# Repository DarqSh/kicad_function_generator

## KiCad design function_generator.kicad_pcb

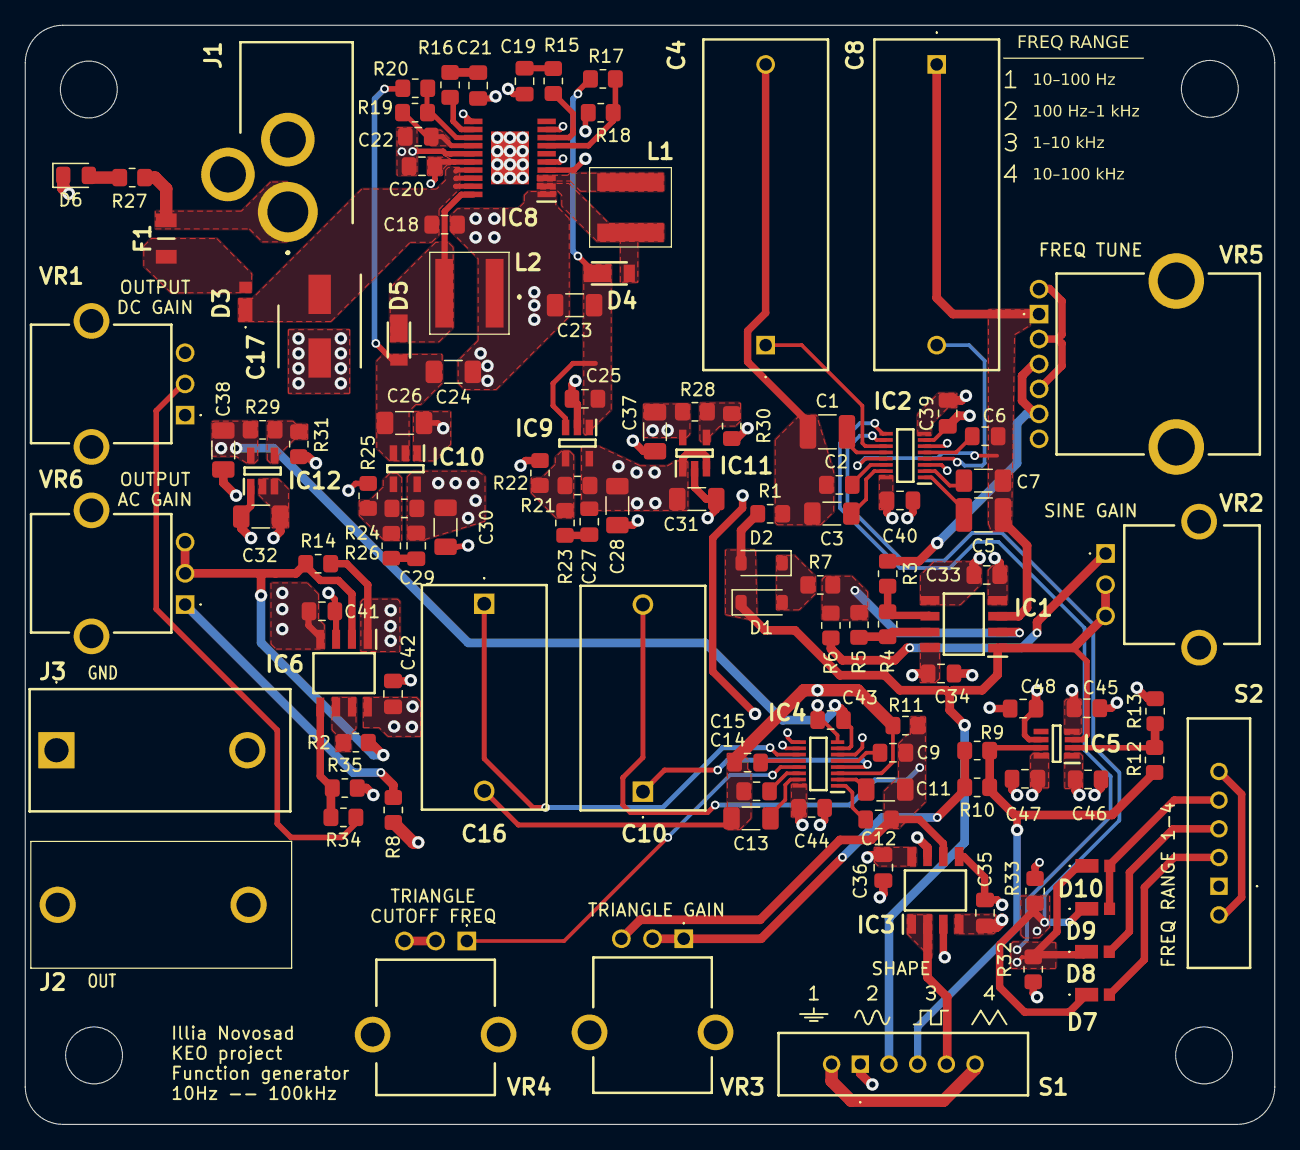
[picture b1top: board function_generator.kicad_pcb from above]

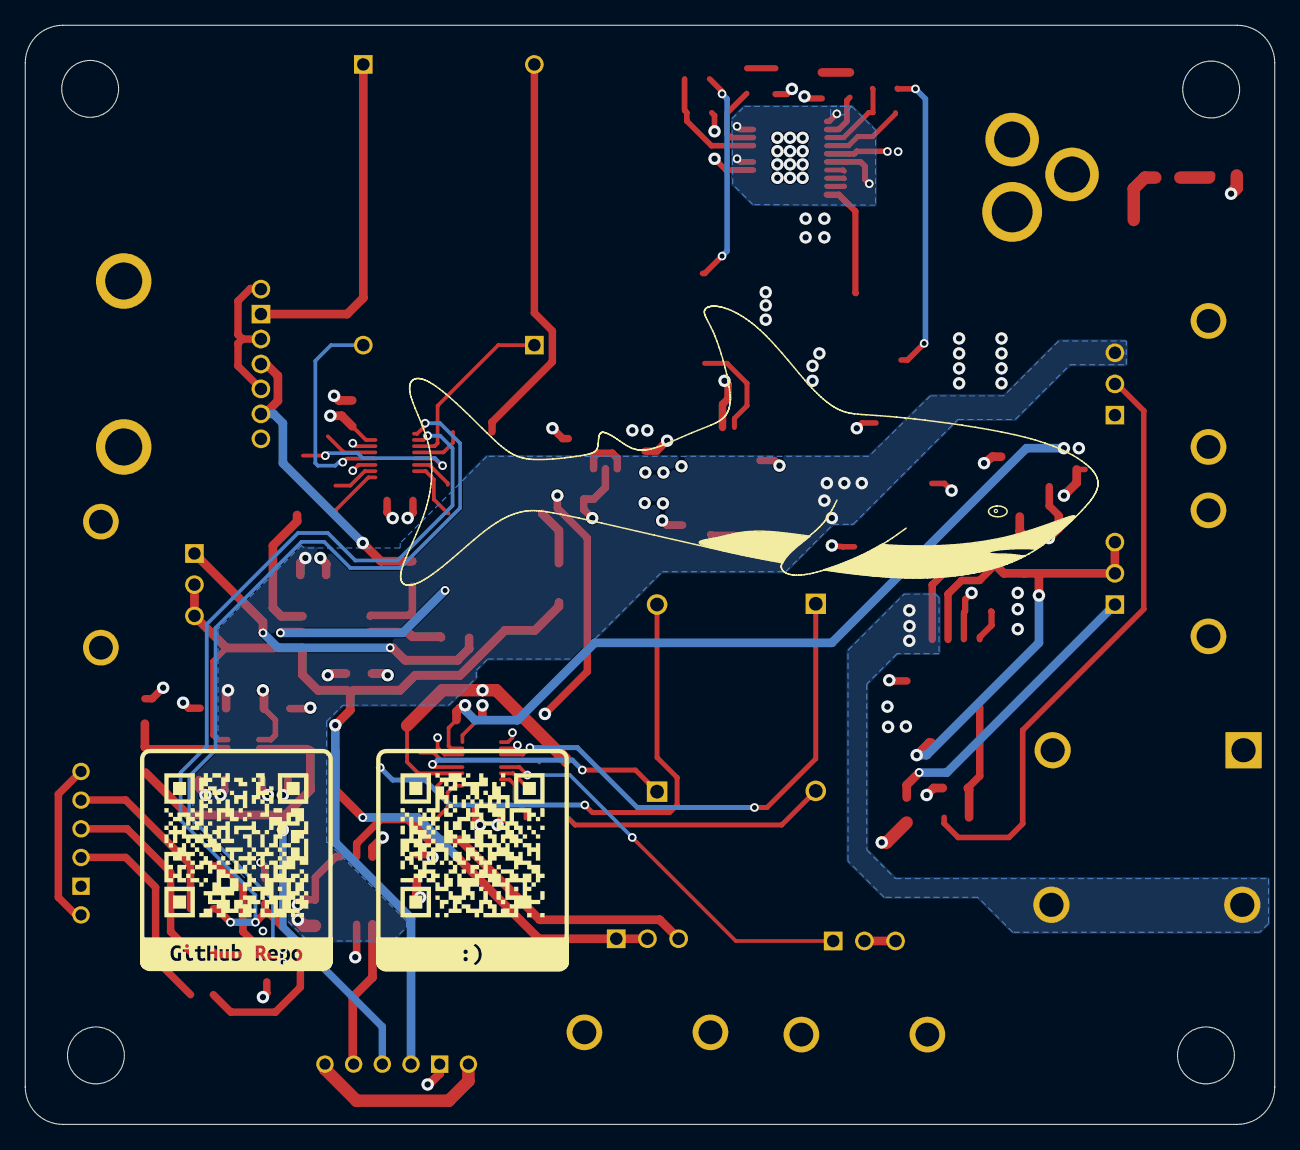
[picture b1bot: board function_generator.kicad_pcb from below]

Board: 4 copper layers, 100.2 x 88.1 mm, 120 parts (2 on the bottom side), 73 nets.

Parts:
C1, C5: 1.5nF; C_1210_3225Metric_Pad1.33x2.70mm_HandSolder
C2, C6: 15nF; C_0805_2012Metric_Pad1.18x1.45mm_HandSolder
C3, C7: 0.15uF; C_1206_3216Metric_Pad1.33x1.80mm_HandSolder
C4, C8: 1.5uF; R75IN415050H4J
C9, C14: 22nF; C_0805_2012Metric_Pad1.18x1.45mm_HandSolder
C10, C16: 2.2uF; 890443325010CS
C11, C13: 0.22uF; C_1206_3216Metric_Pad1.33x1.80mm_HandSolder
C12, C15: 2.2nF; C_0805_2012Metric_Pad1.18x1.45mm_HandSolder
C17: 22uF; CAPAE660X550N
C18, C27, C29, C33, C34, C35, C36, C39, C40, C41, C42, C43, C44, C45, C46, C47, C48: 100nF; C_0805_2012Metric_Pad1.18x1.45mm_HandSolder
C19: 47nF; C_0805_2012Metric_Pad1.18x1.45mm_HandSolder
C20, C22, C25: 1uF; C_0805_2012Metric_Pad1.18x1.45mm_HandSolder
C21: 68nF; C_0805_2012Metric_Pad1.18x1.45mm_HandSolder
C23, C24: 10uF; C_1206_3216Metric_Pad1.33x1.80mm_HandSolder
C26, C28, C30, C31, C32, C37, C38: 2.2uF; C_1206_3216Metric_Pad1.33x1.80mm_HandSolder
D1, D2: D; D_SOD-123
D3, D7, D8, D9, D10: SBA240CH-AU_R1_007A1; SBA240CHAU_R1_007A1
D4, D5: DFLS240-7; POWERDI123
D6: LED; LED_0805_2012Metric_Pad1.15x1.40mm_HandSolder
F1: 0466001.NR; FUSC3215X66N
IC1, IC3: NE5532AD8R2G; SOIC127P600X175-8N
IC2, IC4: TMUX4052DYYRQ1; SOP50P326X110-16N
IC5: TLV1871DDFR; SOT65P280X110-8N
IC6: OPA1656IDR; SOIC127P600X175-8N
IC8: ADP5070AREZ; SOP65P640X120-21N
IC9, IC11: ADP7142AUJZ-R7; SOT95P280X100-5N
IC10, IC12: ADP7182AUJZ-R7; SOT95P280X100-5N
J1: barrel_jack; 694106301002
J2: 571-0500; 5710500
J3: 571-0300; 5710300
L1: 6.8uH; XAL6060682MEC
L2: 15uH; XAL6060153MEC
R1, R4, R5, R6: 3.3k; R_0805_2012Metric_Pad1.20x1.40mm_HandSolder
R2, R14, R32, R33, R35: 10k; R_0805_2012Metric_Pad1.20x1.40mm_HandSolder
R3: 300; R_0805_2012Metric_Pad1.20x1.40mm_HandSolder
R7: 64.9k; R_0805_2012Metric_Pad1.20x1.40mm_HandSolder
R8: 5k; R_0805_2012Metric_Pad1.20x1.40mm_HandSolder
R9, R10: 3.9k; R_0805_2012Metric_Pad1.20x1.40mm_HandSolder
R11, R19, R29: 100k; R_0805_2012Metric_Pad1.20x1.40mm_HandSolder
R12: 330k; R_0805_2012Metric_Pad1.20x1.40mm_HandSolder
R13, R16, R27: 15k; R_0805_2012Metric_Pad1.20x1.40mm_HandSolder
R15: 12k; R_0805_2012Metric_Pad1.20x1.40mm_HandSolder
R17: 2.15M; R_0805_2012Metric_Pad1.20x1.40mm_HandSolder
R18: 113k; R_0805_2012Metric_Pad1.20x1.40mm_HandSolder
R20: 2.1M; R_0805_2012Metric_Pad1.20x1.40mm_HandSolder
R21, R24: 52.3k; R_0805_2012Metric_Pad1.20x1.40mm_HandSolder
R22, R23, R25, R26: 4.64k; R_0805_2012Metric_Pad1.20x1.40mm_HandSolder
R28: 102k; R_0805_2012Metric_Pad1.20x1.40mm_HandSolder
R30, R31: 11.5k; R_0805_2012Metric_Pad1.20x1.40mm_HandSolder
R34: 4.99k; R_0805_2012Metric_Pad1.20x1.40mm_HandSolder
S1, S2: ASLB1470
VR1, VR6: 100k; PTN091V100115K1B
VR2: 1k; PTN091V01115K1B
VR3: 20k; PTN091V20115K1B
VR4: 100k_log; PTN091V100115K1A
VR5: 20k dual-gang; P140KH1Y20AR20K
kobee-studio-6AF0B84B: Kobee Studio; kobee-studio-6AF0B84B
kobee-studio-6AF0B811: Kobee Studio; kobee-studio-6AF0B6D9

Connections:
/+12V_barrel_jack: F1.1, J1.1 (POWER), R27.1
/+12V_for_mux: C37.2, C40.1, C44.1, IC2.16 (VDD), IC4.16 (VDD), IC11.5 (VOUT), R28.1, S2.5 (COM_1), S2.6 (COM_2)
/+15V: C27.2, C28.2, C31.2, C34.1, C36.1, C42.1, C47.1, C48.1, IC1.8 (V+), IC3.8 (V+), IC5.6 (VCCO), IC5.8 (VCCI), IC6.8 (V+), IC9.5 (VOUT), IC11.1 (VIN), IC11.3 (EN), R21.1, VR1.1 (CCW)
/-12V_for_mux: C38.2, C39.1, C43.1, IC2.7 (VSS), IC4.7 (VSS), IC12.5 (VOUT), R29.1
/-15V: C29.2, C30.2, C32.2, C33.1, C35.1, C41.1, C45.1, C46.1, IC1.4 (V-), IC3.4 (V-), IC5.1 (VEEO), IC5.4 (VEEI), IC6.4 (V-), IC10.5 (VOUT), IC12.2 (VIN), IC12.3 (EN), R24.1, VR1.3 (CW)
/mux_choose_0: D7.1 (K), D9.1 (K), IC2.10 (A0), IC4.10 (A0), R33.1
/mux_choose_1: D8.1 (K), D10.1 (K), IC2.9 (A1), IC4.9 (A1), R32.1
/power_supply/LDO+_VIN: C23.1, C25.1, D4.2 (K), IC9.1 (VIN), IC9.3 (EN), R17.1
/power_supply/LDO-_VIN: C24.2, C26.1, D5.1 (A), IC10.2 (VIN), IC10.3 (EN), R20.2
/power_supply/SW2: D5.2 (K), IC8.20 (SW2), L2.2
/power_supply/VREG: C20.1, IC8.5 (SEQ), IC8.9 (EN1), IC8.11 (EN2), IC8.16 (VREG)
/scaling&offset/raw_input: R8.1, S1.5 (COM_1), S1.6 (COM_2)
/scaling&offset/ready_output: IC6.1 (OUT_A), J2.1, J2.2, R14.2
/sine: D1.1 (K), D2.2 (A), IC1.1 (OUTA), IC5.3 (IN-), R1.2, S1.2 (NO_1), VR2.2 (WIPER_), VR2.3 (CW)
/square: IC5.7 (OUT), R9.2, R10.2, R12.1, S1.3 (NO_2)
/triangle: IC3.1 (OUTA), IC3.2 (-INA), S1.4 (NO_3)
/triangle_generator/filtered_triangle: IC3.3 (+INA), IC4.13 (DA), VR4.1 (CCW)
/triangle_generator/unfiltered_triangle: C13.2, C14.2, C15.2, C16.2, IC3.7 (OUTB), IC4.3 (DB), R11.2
GND: C17.2, C18.2, C19.2, C20.2, C21.2, C22.2, C23.2, C24.1, C25.2, C26.2, C28.1, C30.1, C31.1, C32.1, C33.2, C34.2, C35.2, C36.2, C37.1, C38.1, C39.2, C40.2, C41.2, C42.2, C43.2, C44.2, C45.2, C46.2, C47.2, C48.2, D6.1 (K), IC1.5 (+INB), IC2.3 (DB), IC2.6 (~EN), IC2.8 (GND), IC3.5 (+INB), IC4.6 (~EN), IC4.8 (GND), IC6.3 (+IN_A), IC8.1 (PGND), IC8.4 (SYNC/FREQ), IC8.15 (AGND), IC8.21 (EPAD), IC9.2 (GND), IC10.1 (GND), IC11.2 (GND), IC12.1 (GND), J1.2 (GND_1), J1.3 (GND_2), J3.1, J3.2, L2.1, R13.2, R18.2, R22.1, R25.1, R30.1, R31.1, R32.2, R33.2, R35.2, S1.1 (NC), VR4.2 (WIPER), VR4.3 (CW)
unnamed: C1.2, C2.2, C3.2, C4.2, R1.1
unnamed: C19.1, R15.2
unnamed: C21.1, R16.2
unnamed: C27.1, R23.2
unnamed: C29.1, R26.2
unnamed: D1.2 (A), D2.1 (K), R7.2
unnamed: D3.2 (A), F1.2
unnamed: C17.1, C18.1, D3.1 (K), IC8.17 (PVIN1), IC8.18 (PVINSYS), IC8.19 (PVIN2)
unnamed: D4.1 (A), IC8.2 (SW1), L1.2
unnamed: D6.2 (A), R27.2
unnamed: D7.2 (A), S2.2 (NO_1)
unnamed: D8.2 (A), S2.3 (NO_2)
unnamed: D9.2 (A), D10.2 (A), S2.4 (NO_3)
unnamed: C5.1, C6.1, C7.1, C8.1, IC1.3 (+INA), IC2.13 (DA), VR5.R11 (CCW_1)
unnamed: IC1.2 (-INA), R5.2, R6.1, R7.1
unnamed: IC1.6 (-INB), R3.1, R4.2
unnamed: IC1.7 (OUTB), R4.1, R5.1
unnamed: C1.1, IC2.12 (S0A)
unnamed: C5.2, IC2.1 (S0B)
unnamed: C2.1, IC2.14 (S1A)
unnamed: C6.2, IC2.5 (S1B)
unnamed: C3.1, IC2.15 (S2A)
unnamed: C7.2, IC2.2 (S2B)
unnamed: C4.1, IC2.11 (S3A)
unnamed: C8.2, IC2.4 (S3B)
unnamed: C9.2, C10.2, C11.1, C12.1, IC3.6 (-INB), R11.1, VR3.3 (CW)
unnamed: C15.1, IC4.12 (S0A)
unnamed: C12.2, IC4.1 (S0B)
unnamed: C14.1, IC4.14 (S1A)
unnamed: C9.1, IC4.5 (S1B)
unnamed: C13.1, IC4.15 (S2A)
unnamed: C11.2, IC4.2 (S2B)
unnamed: C16.1, IC4.11 (S3A)
unnamed: C10.1, IC4.4 (S3B)
unnamed: IC5.2 (IN+), R12.2, R13.1
unnamed: IC6.5 (+IN_B), R34.2, R35.1
unnamed: IC6.2 (-IN_A), R2.2, R14.1, VR6.2 (WIPER), VR6.3 (CW)
unnamed: IC6.6 (-IN_B), IC6.7 (OUT_B), R2.1
unnamed: IC8.8 (COMP1), R15.1
unnamed: IC8.12 (COMP2), R16.1
unnamed: IC8.7 (FB1), R17.2, R18.1
unnamed: IC8.13 (FB2), R19.2, R20.1
unnamed: IC8.3 (INBK), L1.1
unnamed: C22.1, IC8.14 (VREF), R19.1
unnamed: IC9.4 (SENSE/ADJ), R21.2, R22.2, R23.1
unnamed: IC10.4 (ADJ), R24.2, R25.2, R26.1
unnamed: IC11.4 (SENSE/ADJ), R28.2, R30.2
unnamed: IC12.4 (ADJ), R29.2, R31.2
unnamed: R34.1, VR1.2 (WIPER)
unnamed: R6.2, VR2.1 (CCW)
unnamed: R9.1, R10.1, VR3.1 (CCW), VR3.2 (WIPER_)
unnamed: VR5.R12 (WIPER_1), VR5.R13 (CW_1), VR5.R21 (CCW_2)
unnamed: R3.2, VR5.R22 (WIPER_2), VR5.R23 (CW_2)
unnamed: R8.2, VR6.1 (CCW)

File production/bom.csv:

Designator,Footprint,Quantity,Value,LCSC Part #
"C1, C5",1210,2,1.5nF,
"C10, C16",890443325010CS,2,2.2uF,
"C11, C13",1206,2,0.22uF,
"C12, C15",0805,2,2.2nF,
"C14, C9",0805,2,22nF,
C17,CAPAE660X550N,1,22uF,
"C18, C27, C29, C33, C34, C35, C36, C39, C40, C41, C42, C43, C44, C45, C46, C47, C48",0805,17,100nF,
C19,0805,1,47nF,
"C2, C6",0805,2,15nF,
"C20, C22, C25",0805,3,1uF,
C21,0805,1,68nF,
"C23, C24",1206,2,10uF,
"C26, C28, C30, C31, C32, C37, C38",1206,7,2.2uF,
"C3, C7",1206,2,0.15uF,
"C4, C8",R75IN415050H4J,2,1.5uF,
"D1, D2",D_SOD-123,2,D,
"D10, D3, D7, D8, D9",SBA240CHAU_R1_007A1,5,SBA240CH-AU_R1_007A1,
"D4, D5",POWERDI123,2,DFLS240-7,
D6,0805,1,LED,
F1,FUSC3215X66N,1,0466001.NR,
"IC1, IC3",SOIC127P600X175-8N,2,NE5532AD8R2G,
"IC10, IC12",SOT95P280X100-5N,2,ADP7182AUJZ-R7,
"IC11, IC9",SOT95P280X100-5N,2,ADP7142AUJZ-R7,
"IC2, IC4",SOP50P326X110-16N,2,TMUX4052DYYRQ1,
IC5,SOT65P280X110-8N,1,TLV1871DDFR,
IC6,SOIC127P600X175-8N,1,OPA1656IDR,
IC8,SOP65P640X120-21N,1,ADP5070AREZ,
J1,694106301002,1,barrel_jack,
J2,5710500,1,571-0500,
J3,5710300,1,571-0300,
L1,XAL6060682MEC,1,6.8uH,
L2,XAL6060153MEC,1,15uH,
"R1, R4, R5, R6",0805,4,3.3k,
"R10, R9",0805,2,3.9k,
"R11, R19, R29",0805,3,100k,
R12,0805,1,330k,
"R13, R16, R27",0805,3,15k,
"R14, R2, R32, R33, R35",0805,5,10k,
R15,0805,1,12k,
R17,0805,1,2.15M,
R18,0805,1,113k,
R20,0805,1,2.1M,
"R21, R24",0805,2,52.3k,
"R22, R23, R25, R26",0805,4,4.64k,
R28,0805,1,102k,
R3,0805,1,300,
"R30, R31",0805,2,11.5k,
R34,0805,1,4.99k,
R7,0805,1,64.9k,
R8,0805,1,5k,
"S1, S2",ASLB1470,2,ASLB1470,
"VR1, VR6",PTN091V100115K1B,2,100k,
VR2,PTN091V01115K1B,1,1k,
VR3,PTN091V20115K1B,1,20k,
VR4,PTN091V100115K1A,1,100k_log,
VR5,P140KH1Y20AR20K,1,20k dual-gang,
